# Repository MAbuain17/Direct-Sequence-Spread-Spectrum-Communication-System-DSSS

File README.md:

# DSSS Lab

**Configurable spread-spectrum hardware, receiver experiments and a multiuser CDMA study.**

The project combines a 2 MHz bench implementation with a configurable I/Q board design. Rev A integrates an STM32G474, dual DAC outputs, receive inputs and digital expansion around a programmable signal chain.

## Configurable hardware — Rev A

| Area | Design |
|---|---|
| Data | User bits, text, hexadecimal payloads, PRBS and repeating patterns |
| Spreading | Selectable LFSR taps, seed, code phase and spreading length; uploaded sequences |
| Modulation | BPSK, QPSK, OOK and continuous-phase 2-FSK in the firmware specification |
| Analogue | Buffered TX I/Q, filtered and protected RX I/Q, four labelled SMA ports |
| Control | USB-C, reset/mode/user buttons, status LEDs and test points |
| Development | SWD/SWO programming, SPI/UART expansion, chip/data/PN/frame signals |
| PCB | 110 × 80 mm, four copper layers, routed nets, ground planes and M3 mounting holes |

The [hardware package](hardware/configurable/README.md) includes the schematic, routed PCB, board renders, component list and control interface.

## Explore the project

| Topic | Open |
|---|---|
| PCB architecture, BOM and renders | [Configurable hardware](hardware/configurable/README.md) |
| Signal modes and USB commands | [Control interface](hardware/configurable/control-interface.md) |
| Original bench build and captures | [Laboratory implementation](hardware/README.md) |
| BER, interference and synchronization | [Simulation results](docs/results.md) |
| Multiuser access, near–far and receiver algorithms | [CDMA extension](docs/cdma.md) |
| Interactive code and receiver study | [CDMA signal explorer](visualizer/index.html) |
| Signal-chain conventions and parameters | [Methodology](docs/methodology.md) |
| Python, MATLAB and Octave setup | [Getting started](docs/getting-started.md) |

## Run Python

From the repository root, using Python 3.10 or later:

```bash
python -m pip install -e .
python -m unittest discover -s tests -v
python examples/burst_link.py
python -m dsss_lab.experiments
python examples/pulse_shaping.py
python examples/cdma_study.py
```

For a smaller run, add `--quick` to the experiment command. CSV files, figures and environment metadata are written to `results/`. Running without installing is also possible with `PYTHONPATH=src` on Linux/macOS; see the Windows guide for PowerShell.

## Run MATLAB

No Communications Toolbox is required. From the repository root:

```matlab
addpath('matlab');
test_dsss;
run_experiments('results/matlab', 12000);
advanced_demo('results/matlab');
```

MATLAB shares deterministic test vectors with Python. Random-number streams differ, so Monte Carlo results should agree statistically, not bit-for-bit. **Python, GNU Octave and native MATLAB pass the published GitHub Actions validation workflows.** Native MATLAB runs automatically when its implementation, shared vectors or workflow changes and remains manually dispatchable.

## What the software explores

| Area | Implemented experiments |
|---|---|
| Data | Random bits, constants, alternating patterns, bursts, UTF-8 text, 8-bit PCM, CRC32 frames |
| Spreading | Exact hardware XNOR recurrence, code phase, autocorrelation, configurable spreading length, two-user Gold-family interference |
| Channels | AWGN; in-band and out-of-band tones; swept interference; burst noise; multipath; symbol-independent Rayleigh fading |
| Receiver | Coherent despreading, known-preamble delay/CFO acquisition, burst phase correction, known-channel matched combining |
| Front end | Carrier offset, phase offset/noise, fractional timing error, ADC clipping/quantization, IQ imbalance, RRC pulse shaping |
| Measurements | BER with Wilson intervals, frame CRC failure rate, acquisition success, raw decision EVM, Welch PSD and 99% occupied bandwidth |
| Coding | Soft repetition decoding with equal information-bit energy as a normalization check |

## BER and interference

At equal information-bit energy, DSSS and ordinary coherent BPSK have the same theoretical BER in AWGN. Spreading's interference behaviour depends on the interferer's spectrum and the receiver. The experiments include cases where DSSS helps and cases where the narrower unspread receiver performs better.

The simulation uses 60,000 bits per AWGN point and 30,000 bits per interference point. Source CSVs include error counts and confidence intervals; seeds and model settings are documented in [methodology](docs/methodology.md).

## From DSSS to CDMA

The [CDMA extension](docs/cdma.md) combines four spread-spectrum users in one channel and compares a matched filter, decorrelator and linear MMSE receiver under code-phase and near–far changes. The sweep records 45 conditions with 12,000 desired-user bits each. A separate [browser explorer](visualizer/index.html) exposes the code correlations, chip waveforms and receiver decisions interactively.

To use the explorer, download or clone the repository and open `visualizer/index.html` in a browser.

## Credits

Project by **Mohamed Abuain**. The university bench implementation was supervised by Prof. Tammam Benmusa. Its circuit reference and source article are recorded in the [design references](docs/attribution.md).

[Software licence](LICENSE.md) · [Changelog](CHANGELOG.md) · [Roadmap](docs/roadmap.md)

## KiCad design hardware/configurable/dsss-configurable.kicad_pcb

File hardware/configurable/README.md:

# Configurable DSSS transceiver — Rev A

A USB-controlled I/Q baseband board built around the STM32G474RET6. The architecture replaces fixed logic with programmable data generation, spreading and symbol mapping, while exposing both analogue channels and digital timing signals for measurement.

**Design:** 110 × 80 mm · four copper layers · 70 circuit components · four SMA ports · USB-C · SWD · SPI/UART expansion.

## Configurable signal chain

```mermaid
flowchart LR
    H[USB host: payload and configuration] --> P[Payload / preamble / CRC]
    P --> S[Programmable spreading]
    N[LFSR taps, seed, length and phase] --> S
    S --> M[BPSK / QPSK / OOK / 2-FSK mapping]
    M --> D[Timer-triggered dual DAC + DMA]
    D --> T[RC filters + I/Q buffers]
    T --> O[TX I / TX Q]
    I[RX I / RX Q] --> A[Input resistors, clamps and RC filters]
    A --> B[Receive buffers + dual ADC]
    B --> R[DMA capture / host analysis]
    S --> G[Chip clock / data / PN / frame header]
```

## Planned operating controls

| Control | Options |
|---|---|
| Payload | User bit string, hexadecimal bytes, UTF-8 text, PRBS, alternating bits, all-zero/all-one and repeating patterns |
| PN sequence | Configurable Fibonacci LFSR order, feedback taps, seed, code phase and spreading length; optional uploaded chip sequence |
| Modulation | BPSK, Gray-mapped QPSK, OOK and continuous-phase 2-FSK |
| Timing | Chip rate, samples per chip, burst duration, frame spacing and repeat count |
| Framing | Preamble, length, payload and CRC32; raw chip mode for scope captures |
| Experiments | I/Q loopback, code mismatch, delay sweeps, burst acquisition and known-pattern BER comparisons |
| Instrumentation | Digital chip clock, data, PN and frame signals; DAC/ADC test pads; status LEDs |

Rev A includes the schematic, routed PCB and control specification. Firmware and board bring-up are the next development stage. The Python/MATLAB simulations remain available for numerical experiments.

## Hardware blocks

| Block | Implementation |
|---|---|
| Processing | STM32G474RET6, LQFP64; Cortex-M4 with hardware timers, DMA, dual DAC and multiple ADCs |
| USB | GCT USB4105 USB-C connector, separate 5.1 kΩ CC pull-downs, USBLC6 protection and 22 Ω data-line resistors |
| Power | USB 5 V, 500 mA PTC, AP2112K 3.3 V regulator; ferrite-filtered analogue rail and local decoupling |
| Clock | 8 MHz crystal with load capacitors; USB clock configuration described in the firmware plan |
| Transmit | PA4/PA5 DAC outputs, 1 kΩ / 1 nF RC filters, TLV9064 unity-gain buffers and 100 Ω output isolation |
| Receive | Series input resistance, Schottky clamps, 1 kΩ / 1 nF RC filtering, TLV9064 buffers and PC0/PC1 ADC inputs |
| Development | SWD/SWO, reset button, boot jumper, mode/user buttons, TX/RX LEDs and SPI/UART header |
| Mechanical | Four M3 mounting holes, separated USB/power, processing and analogue regions, labelled SMA ports |

The SMA connections carry **DC-biased baseband I/Q**, with high-impedance loading. They are not antenna outputs or 50 Ω line drivers. The default development target is 25 kchip/s at four samples/chip; the analogue RC corner is approximately 159 kHz. Rate limits depend on firmware timing, conversion settings and filter response.

## Design files

| File | Contents |
|---|---|
| [KiCad project](dsss-configurable.kicad_pro) | Board rules and project settings |
| [Schematic](dsss-configurable.kicad_sch) | Connected component-level design |
| [PCB](dsss-configurable.kicad_pcb) | Four-layer layout, copper tracks, vias and filled ground planes |
| [Local symbol library](dsss-configurable.kicad_sym) | Embedded component symbols for the project |
| [Schematic preview](renders/schematic.svg) | Browser-readable circuit drawing |
| [Top view](renders/board-top.png) | Component placement and silkscreen |
| [Copper view](renders/copper.svg) | Routed layout |
| [Bill of materials](bom.csv) | References, values and footprints |
| [Pin map](pin-map.md) | MCU peripheral and connector assignments |
| [Control interface](control-interface.md) | Proposed USB commands, modes and frame format |
| [Design review](design-review.md) | Connectivity checks and next review items |

Open `dsss-configurable.kicad_pro` in KiCad 10. The standard footprint and 3D model libraries supply the component geometry; the local symbol library is included in the project.

## Component references

- [ST STM32G474RE datasheet](https://www.st.com/resource/en/datasheet/stm32g474re.pdf)
- [TI TLV9064](https://www.ti.com/product/TLV9064)
- [Diodes AP2112 datasheet](https://www.diodes.com/datasheet/download/AP2112.pdf)

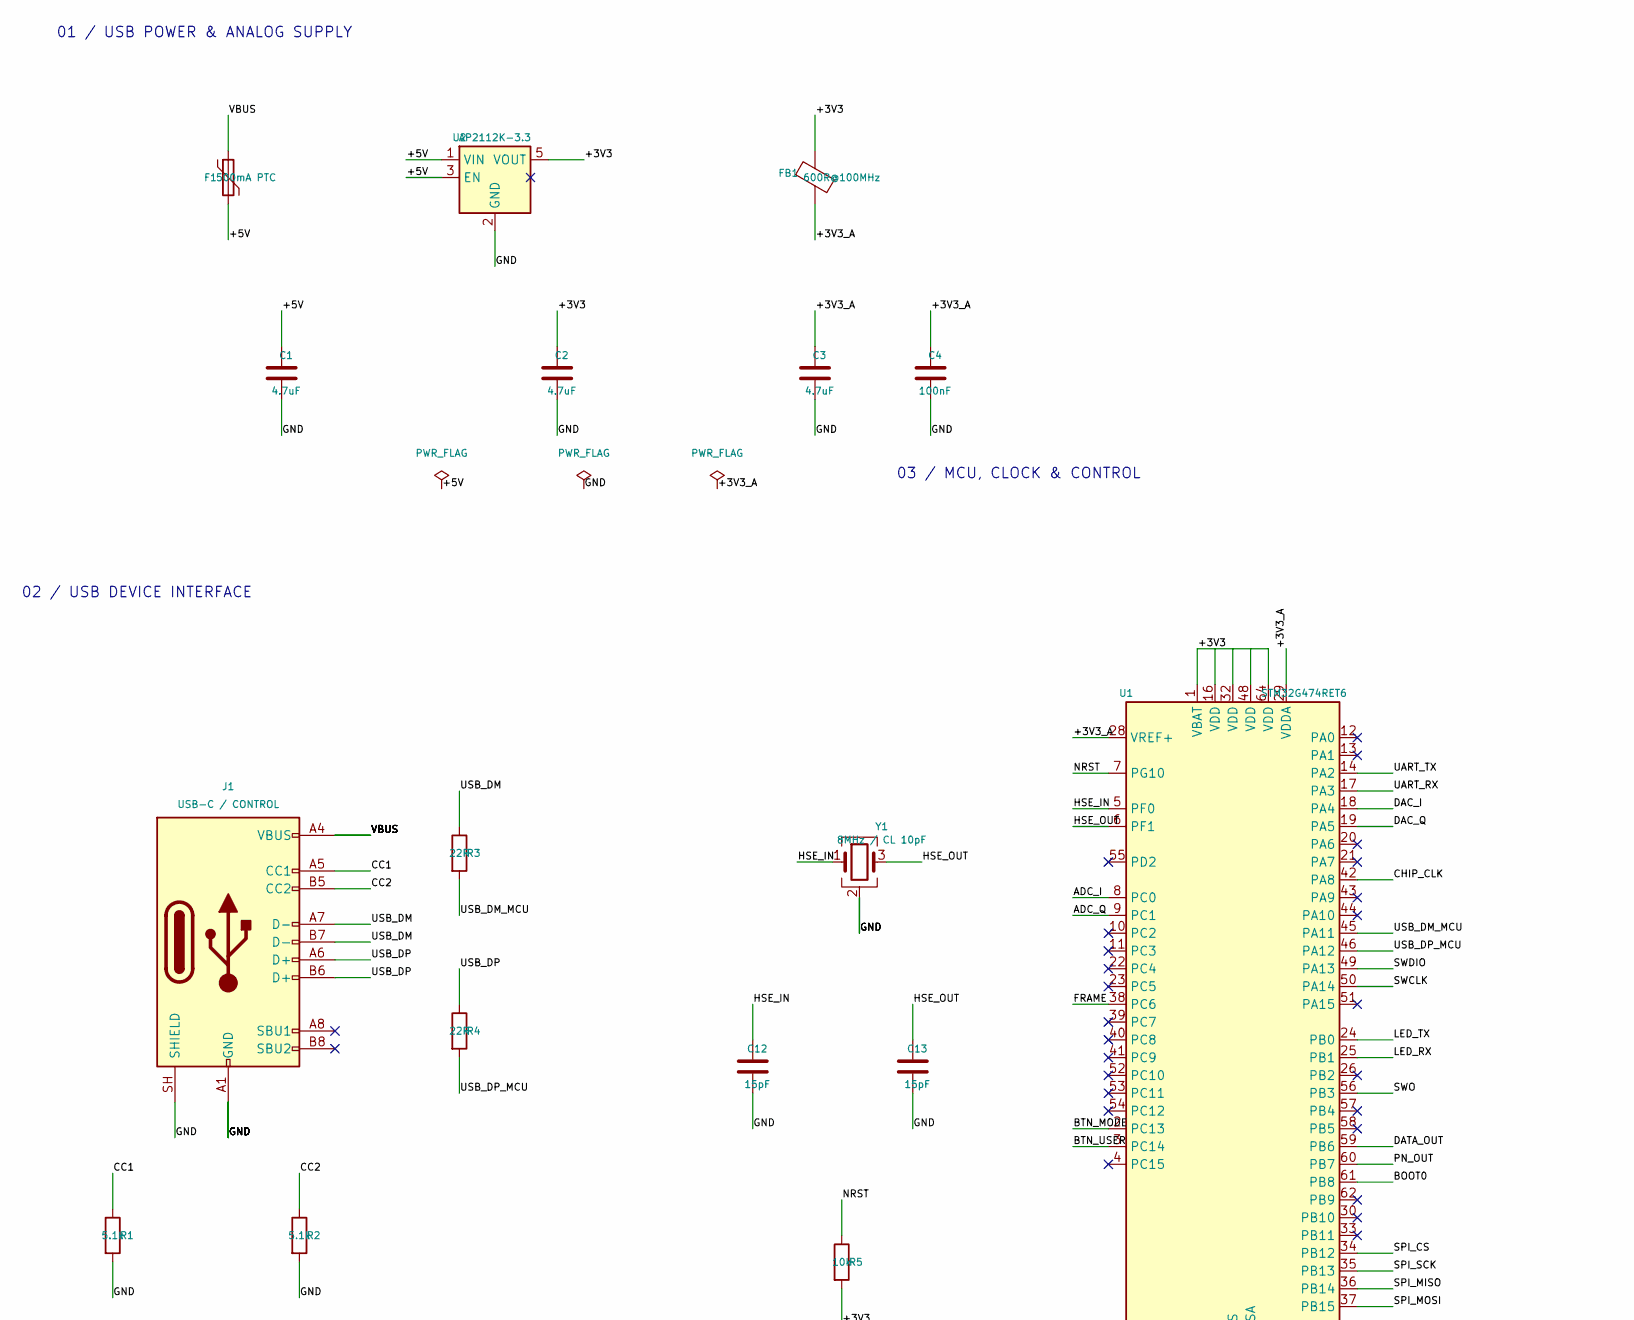
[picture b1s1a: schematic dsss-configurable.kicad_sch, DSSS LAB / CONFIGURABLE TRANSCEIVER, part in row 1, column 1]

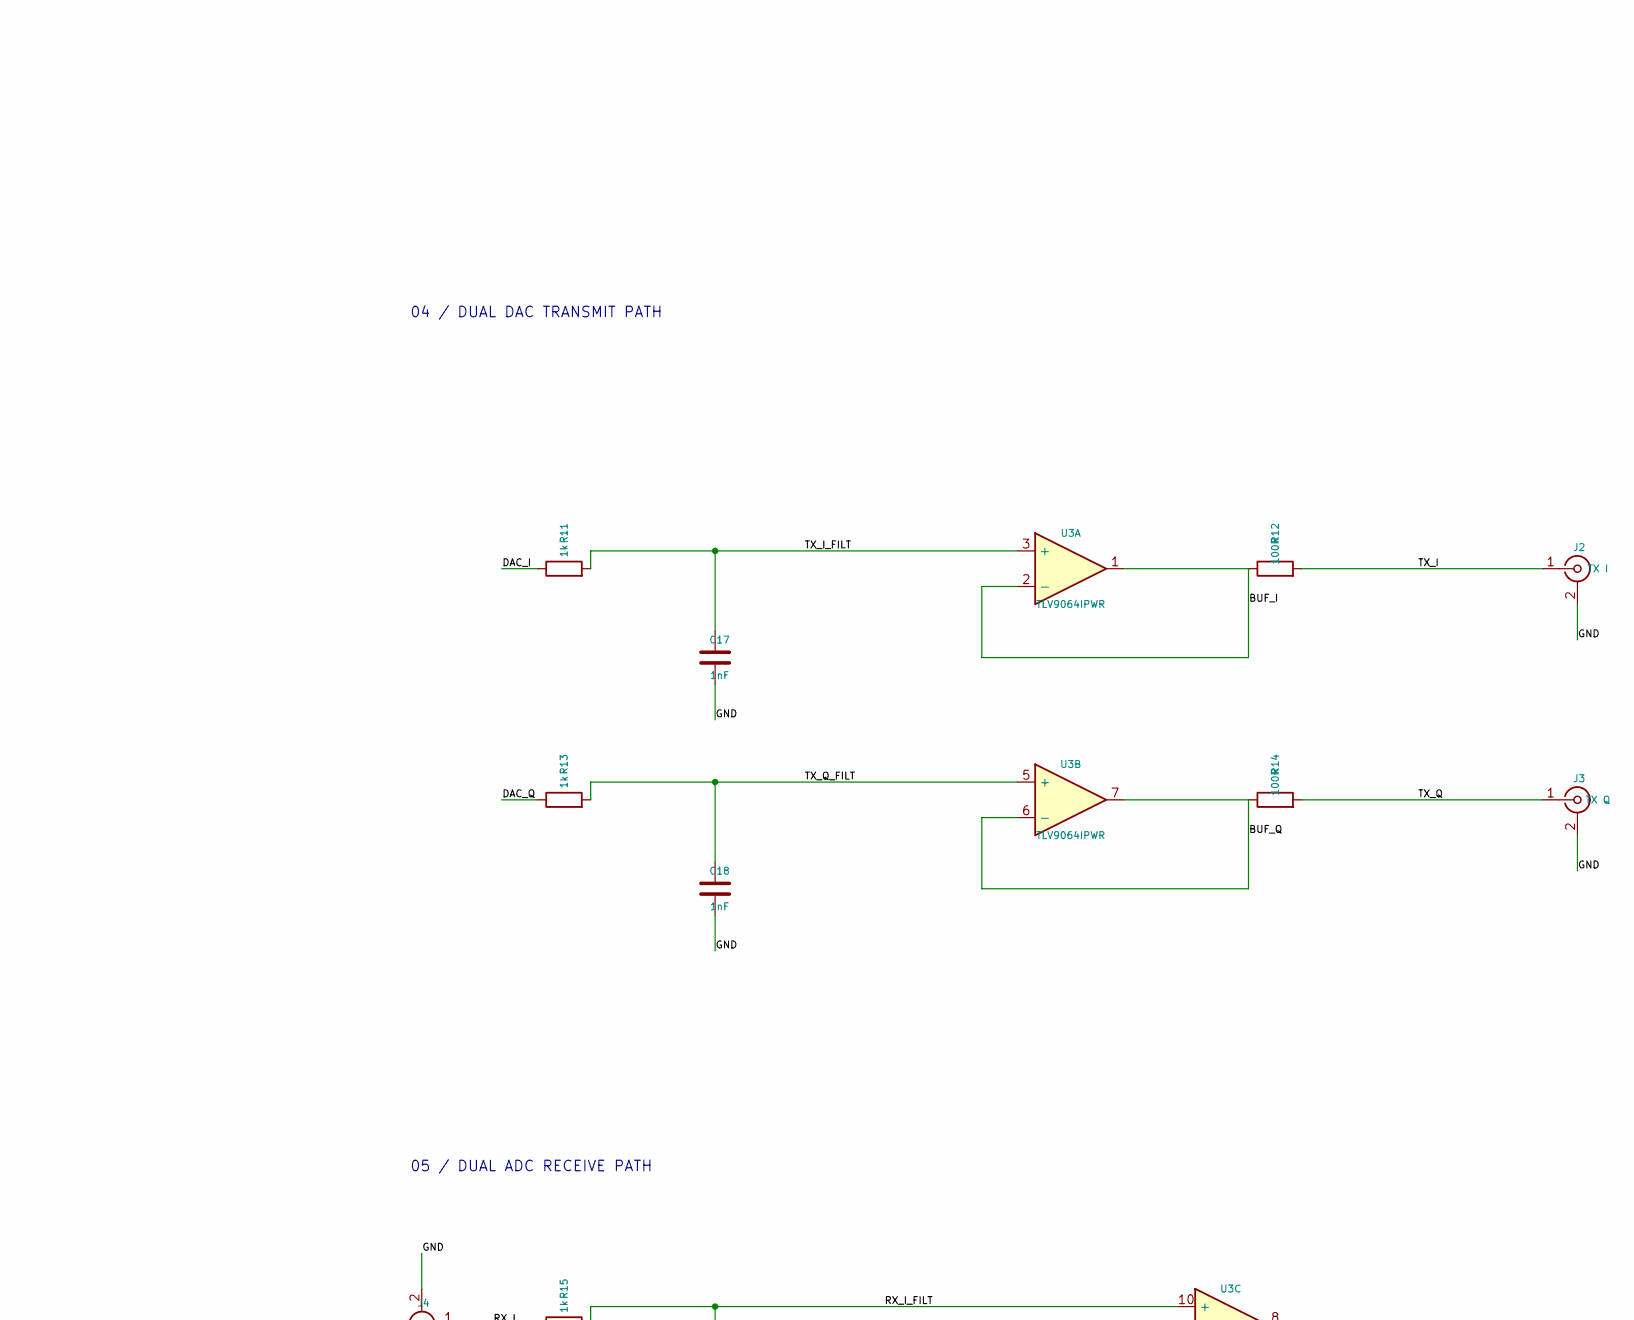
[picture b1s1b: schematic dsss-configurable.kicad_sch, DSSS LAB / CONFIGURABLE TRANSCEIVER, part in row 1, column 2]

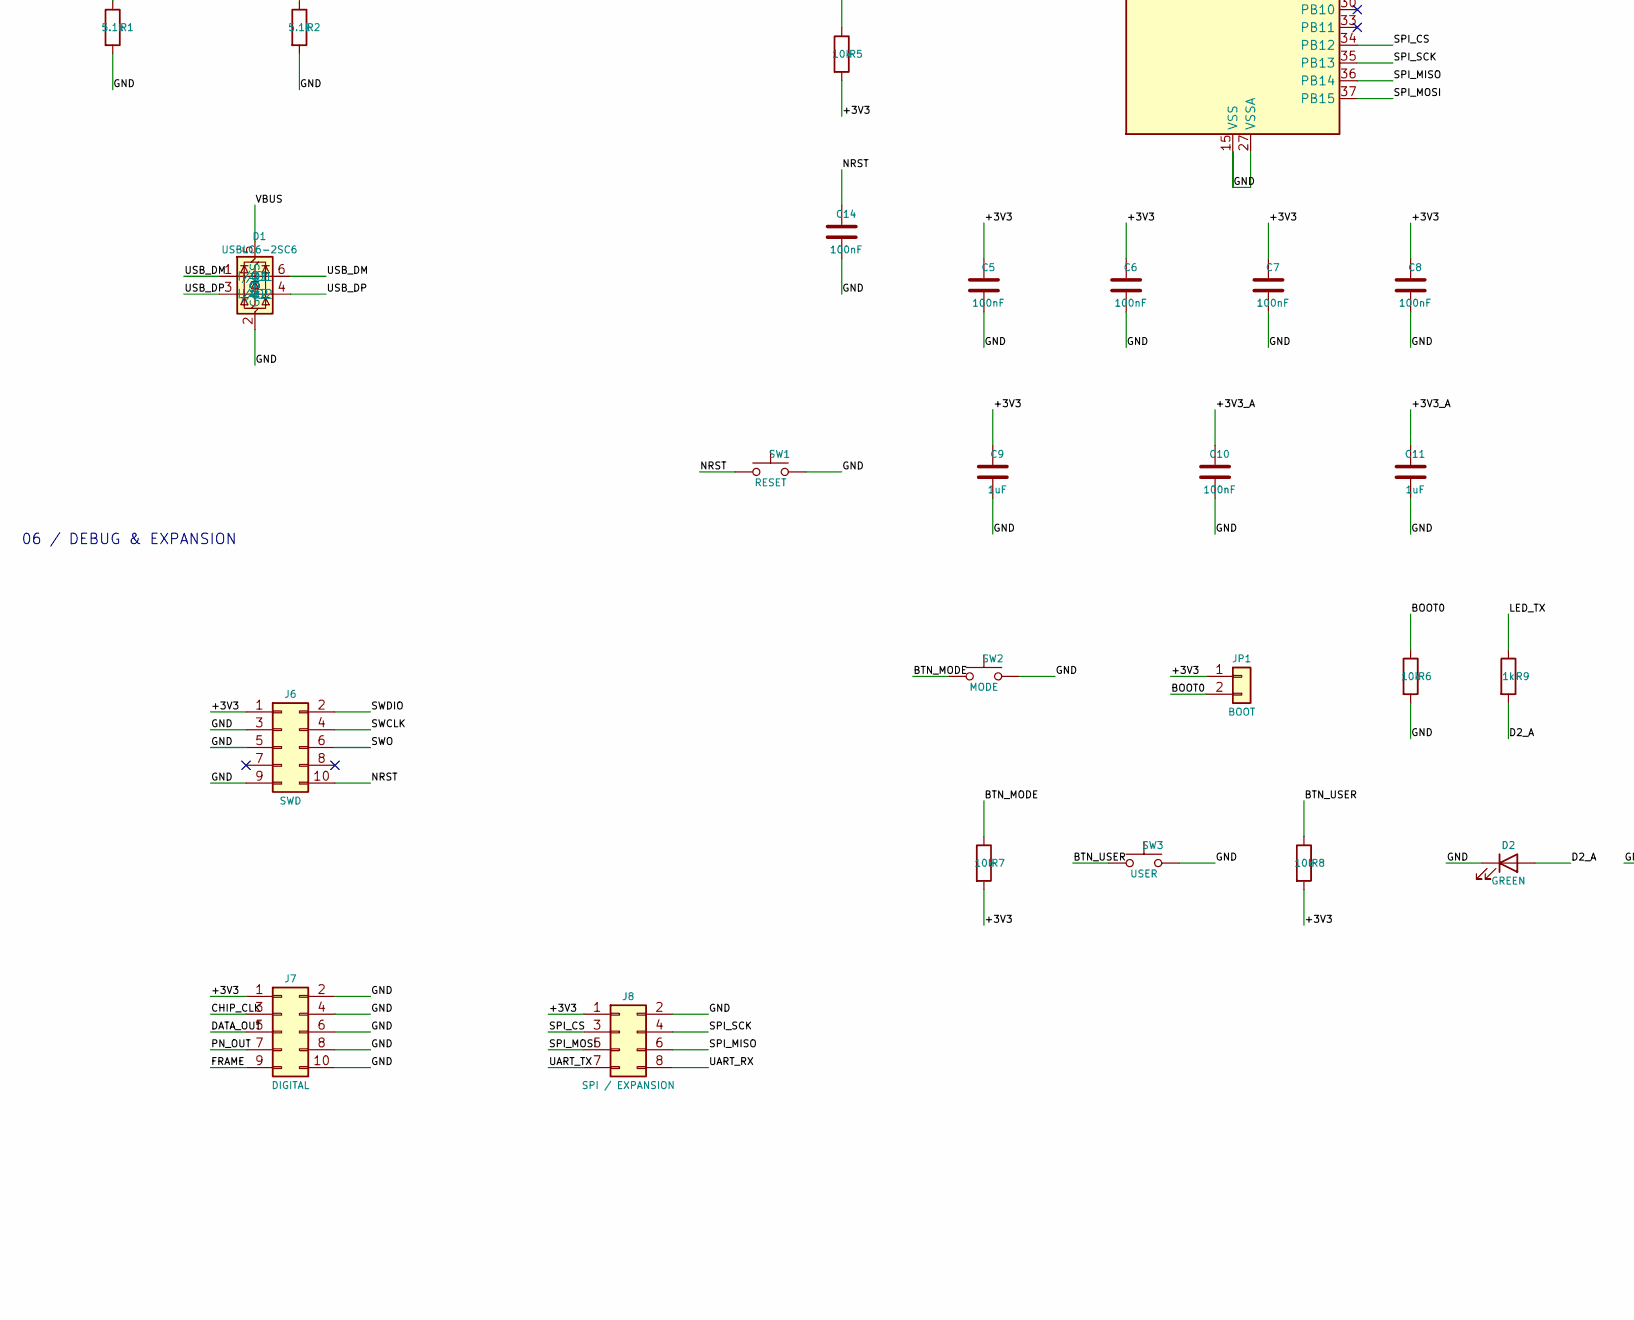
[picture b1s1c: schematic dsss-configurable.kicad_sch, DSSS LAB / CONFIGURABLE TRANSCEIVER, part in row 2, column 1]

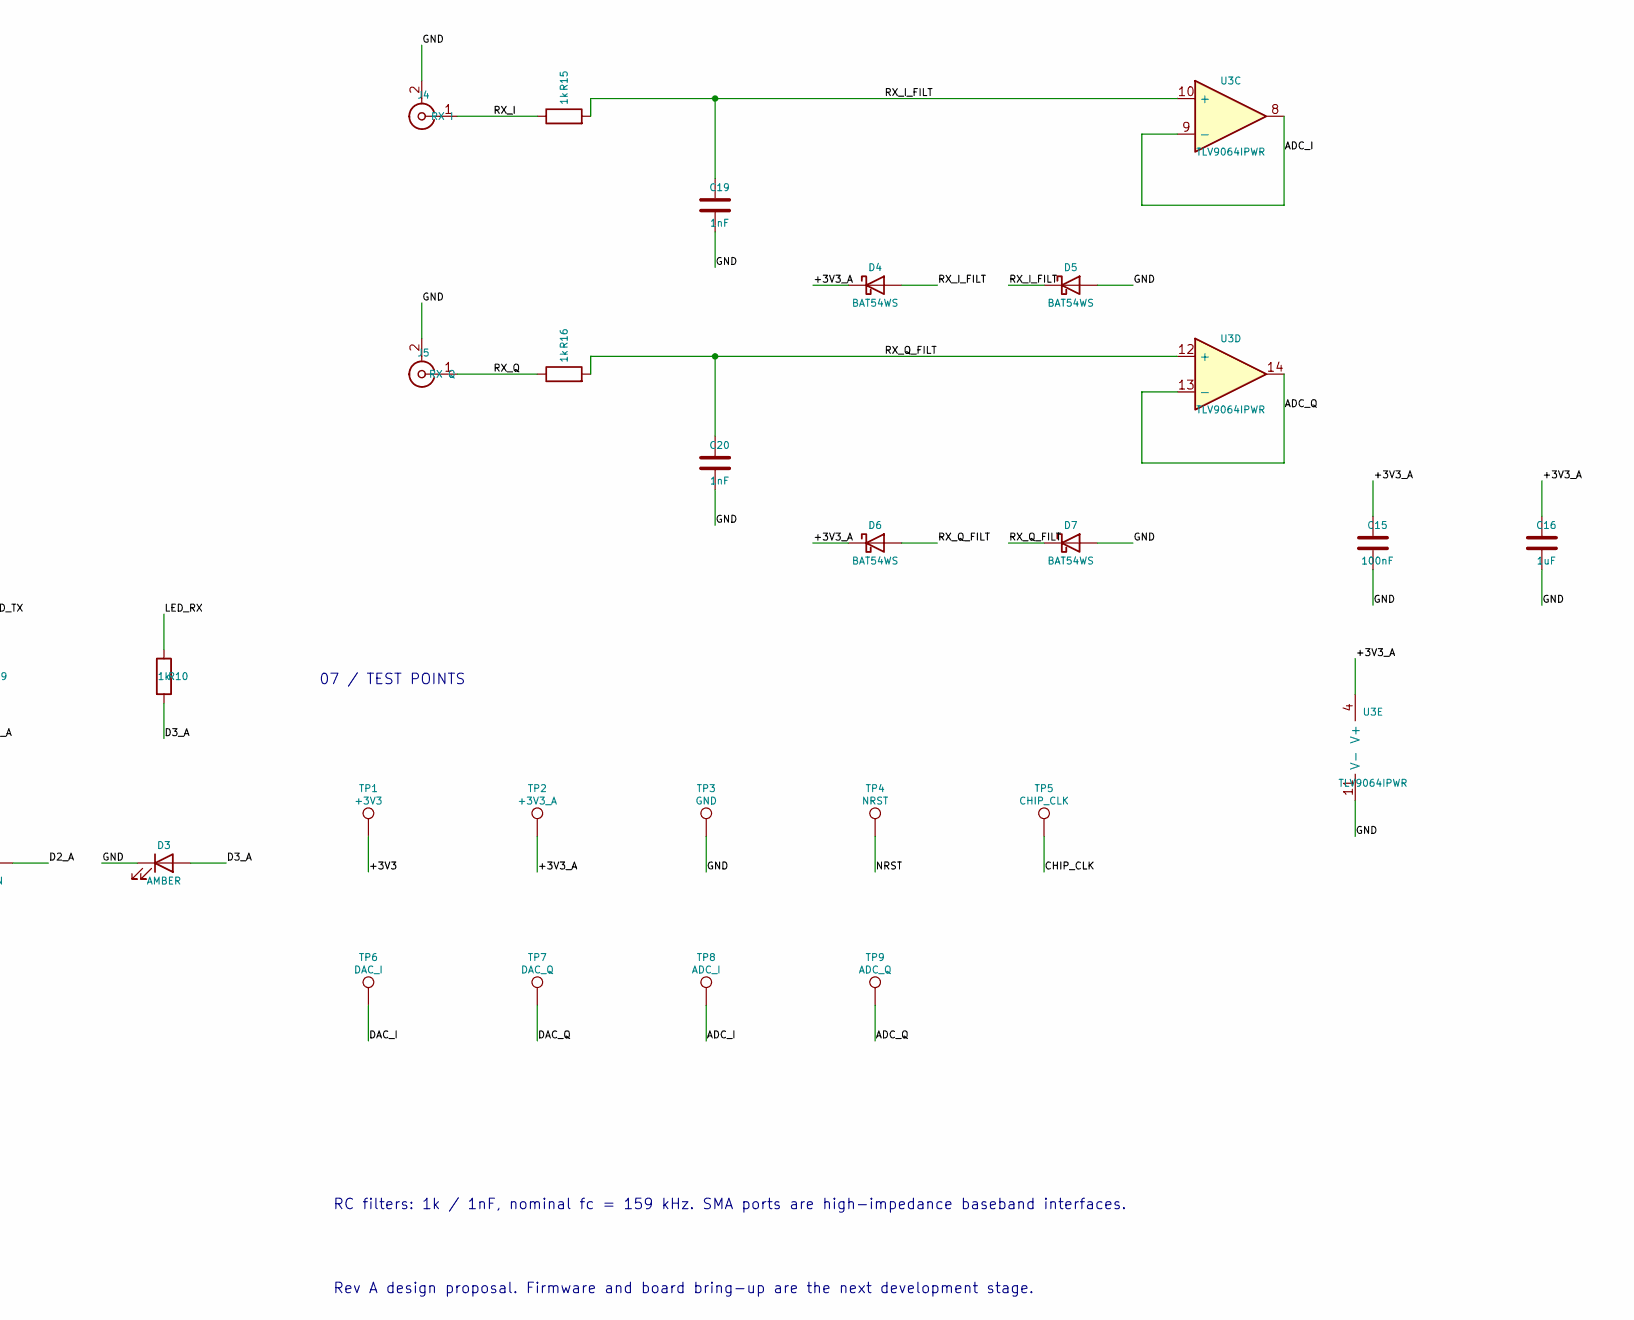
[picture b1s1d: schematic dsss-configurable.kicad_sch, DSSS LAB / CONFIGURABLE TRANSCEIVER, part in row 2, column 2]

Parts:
C1, C2, C3: 4.7uF; C_0603_1608Metric
C4, C5, C6, C7, C8, C10, C14, C15: 100nF; C_0603_1608Metric
C9, C11, C16: 1uF; C_0603_1608Metric
C12, C13: 15pF; C_0603_1608Metric
C17, C18, C19, C20: 1nF; C_0603_1608Metric
D1: USBLC6-2SC6; SOT-23-6
D2: GREEN; LED_0603_1608Metric
D3: AMBER; LED_0603_1608Metric
D4, D5, D6, D7: BAT54WS; D_SOD-323
F1: 500mA PTC; Fuse_1206_3216Metric
FB1: 600R@100MHz; R_0603_1608Metric
J1: USB-C / CONTROL; USB_C_Receptacle_GCT_USB4105-xx-A_16P_TopMnt_Horizontal
J2: TX I; SMA_Amphenol_132291_Vertical
J3: TX Q; SMA_Amphenol_132291_Vertical
J4: RX I; SMA_Amphenol_132291_Vertical
J5: RX Q; SMA_Amphenol_132291_Vertical
J6: SWD; PinHeader_2x05_P1.27mm_Vertical
J7: DIGITAL; PinHeader_2x05_P2.54mm_Vertical
J8: SPI / EXPANSION; PinHeader_2x04_P2.54mm_Vertical
JP1: BOOT; PinHeader_1x02_P2.54mm_Vertical
R1, R2: 5.1k; R_0603_1608Metric
R3, R4: 22R; R_0603_1608Metric
R5, R6, R7, R8: 10k; R_0603_1608Metric
R9, R10, R11, R13, R15, R16: 1k; R_0603_1608Metric
R12, R14: 100R; R_0603_1608Metric
SW1: RESET; SW_SPST_TL3342
SW2: MODE; SW_SPST_TL3342
SW3: USER; SW_SPST_TL3342
TP1: +3V3; TestPoint_Pad_D1.5mm
TP2: +3V3_A; TestPoint_Pad_D1.5mm
TP3: GND; TestPoint_Pad_D1.5mm
TP4: NRST; TestPoint_Pad_D1.5mm
TP5: CHIP_CLK; TestPoint_Pad_D1.5mm
TP6: DAC_I; TestPoint_Pad_D1.5mm
TP7: DAC_Q; TestPoint_Pad_D1.5mm
TP8: ADC_I; TestPoint_Pad_D1.5mm
TP9: ADC_Q; TestPoint_Pad_D1.5mm
U1: STM32G474RET6; LQFP-64_10x10mm_P0.5mm
U2: AP2112K-3.3; SOT-23-5
U3: TLV9064IPWR; TSSOP-14_4.4x5mm_P0.65mm
Y1: 8MHz / CL 10pF; Crystal_SMD_3225-4Pin_3.2x2.5mm

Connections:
+3V3: C2.1, C5.1, C6.1, C7.1, C8.1, C9.1, FB1.1, J6.1, J7.1, J8.1, JP1.1, R5.2, R7.2, R8.2, TP1.1, U1.1 (VBAT), U1.16 (VDD), U1.32 (VDD), U1.48 (VDD), U1.64 (VDD), U2.5 (VOUT)
+3V3_A: C3.1, C4.1, C10.1, C11.1, C15.1, C16.1, D4.1 (K), D6.1 (K), FB1.2, TP2.1, U1.28 (VREF+), U1.29 (VDDA), U3.4 (V+)
+5V: C1.1, F1.2, U2.1 (VIN), U2.3 (EN)
ADC_I: TP8.1, U1.8 (PC0), U3.8, U3.9 (-)
ADC_Q: TP9.1, U1.9 (PC1), U3.13 (-), U3.14
BOOT0: JP1.2, R6.1, U1.61 (PB8)
BTN_MODE: R7.1, SW2.1, U1.2 (PC13)
BTN_USER: R8.1, SW3.1, U1.3 (PC14)
BUF_I: R12.1, U3.1, U3.2 (-)
BUF_Q: R14.1, U3.6 (-), U3.7
CC1: J1.A5 (CC1), R1.1
CC2: J1.B5 (CC2), R2.1
CHIP_CLK: J7.3, TP5.1, U1.42 (PA8)
D2_A: D2.2 (A), R9.2
D3_A: D3.2 (A), R10.2
DAC_I: R11.1, TP6.1, U1.18 (PA4)
DAC_Q: R13.1, TP7.1, U1.19 (PA5)
DATA_OUT: J7.5, U1.59 (PB6)
FRAME: J7.9, U1.38 (PC6)
GND: C1.2, C2.2, C3.2, C4.2, C5.2, C6.2, C7.2, C8.2, C9.2, C10.2, C11.2, C12.2, C13.2, C14.2, C15.2, C16.2, C17.2, C18.2, C19.2, C20.2, D1.2 (GND), D2.1 (K), D3.1 (K), D5.2 (A), D7.2 (A), J1.A1 (GND), J1.A12 (GND), J1.B1 (GND), J1.B12 (GND), J1.SH (SHIELD), J2.2 (Ext), J3.2 (Ext), J4.2 (Ext), J5.2 (Ext), J6.3, J6.5, J6.9, J7.2, J7.4, J7.6, J7.8, J7.10, J8.2, R1.2, R2.2, R6.2, SW1.2, SW2.2, SW3.2, TP3.1, U1.15 (VSS), U1.27 (VSSA), U1.31 (VSS), U1.47 (VSS), U1.63 (VSS), U2.2 (GND), U3.11 (V-), Y1.2 (G), Y1.4 (G)
HSE_IN: C12.1, U1.5 (PF0), Y1.1
HSE_OUT: C13.1, U1.6 (PF1), Y1.3
LED_RX: R10.1, U1.25 (PB1)
LED_TX: R9.1, U1.24 (PB0)
NRST: C14.1, J6.10, R5.1, SW1.1, TP4.1, U1.7 (PG10)
PN_OUT: J7.7, U1.60 (PB7)
RX_I: J4.1 (In), R15.1
RX_I_FILT: C19.1, D4.2 (A), D5.1 (K), R15.2, U3.10 (+)
RX_Q: J5.1 (In), R16.1
RX_Q_FILT: C20.1, D6.2 (A), D7.1 (K), R16.2, U3.12 (+)
SPI_CS: J8.3, U1.34 (PB12)
SPI_MISO: J8.6, U1.36 (PB14)
SPI_MOSI: J8.5, U1.37 (PB15)
SPI_SCK: J8.4, U1.35 (PB13)
SWCLK: J6.4, U1.50 (PA14)
SWDIO: J6.2, U1.49 (PA13)
SWO: J6.6, U1.56 (PB3)
TX_I: J2.1 (In), R12.2
TX_I_FILT: C17.1, R11.2, U3.3 (+)
TX_Q: J3.1 (In), R14.2
TX_Q_FILT: C18.1, R13.2, U3.5 (+)
UART_RX: J8.8, U1.17 (PA3)
UART_TX: J8.7, U1.14 (PA2)
USB_DM: D1.1 (I/O1), D1.6 (I/O1), J1.A7 (D-), J1.B7 (D-), R3.1
USB_DM_MCU: R3.2, U1.45 (PA11)
USB_DP: D1.3 (I/O2), D1.4 (I/O2), J1.A6 (D+), J1.B6 (D+), R4.1
USB_DP_MCU: R4.2, U1.46 (PA12)
VBUS: D1.5 (VBUS), F1.1, J1.A4 (VBUS), J1.A9 (VBUS), J1.B4 (VBUS), J1.B9 (VBUS)

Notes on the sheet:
01 / USB POWER & ANALOG SUPPLY
02 / USB DEVICE INTERFACE
03 / MCU, CLOCK & CONTROL
04 / DUAL DAC TRANSMIT PATH
05 / DUAL ADC RECEIVE PATH
06 / DEBUG & EXPANSION
07 / TEST POINTS
RC filters: 1k / 1nF, nominal fc = 159 kHz. SMA ports are high-impedance baseband interfaces.
Rev A design proposal. Firmware and board bring-up are the next development stage.

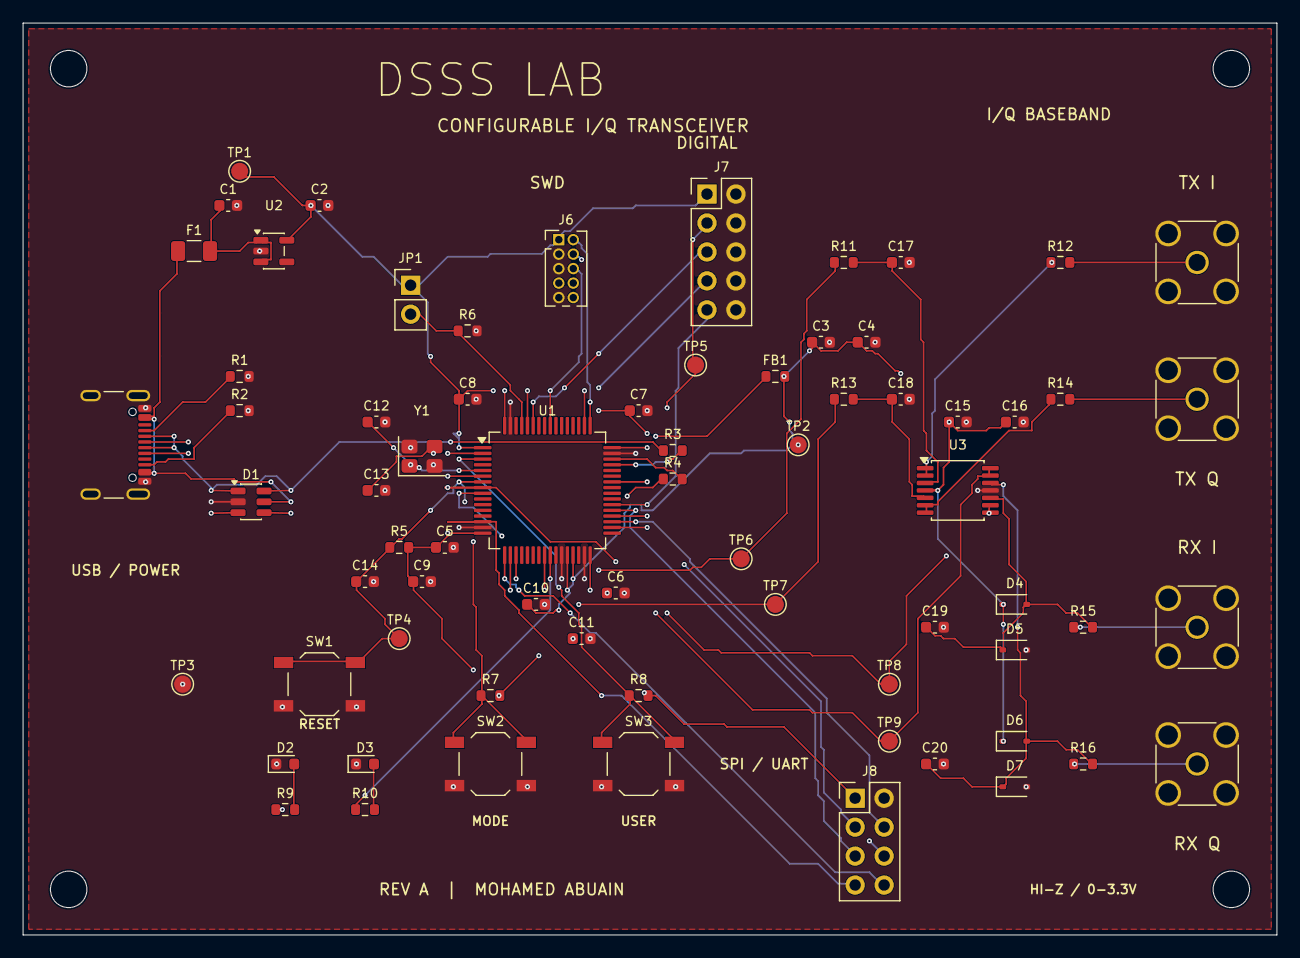
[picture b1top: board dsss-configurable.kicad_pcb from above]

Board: 4 copper layers, 110.0 x 80.0 mm, 74 parts (0 on the bottom side), 48 nets.

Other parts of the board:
H1, H2, H3, H4: MountingHole_3.2mm_M3

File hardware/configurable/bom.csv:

Reference,Value / part,Footprint,Description
J1,USB-C / CONTROL,Connector_USB:USB_C_Receptacle_GCT_USB4105-xx-A_16P_TopMnt_Horizontal,
F1,500mA PTC,Fuse:Fuse_1206_3216Metric,
U2,AP2112K-3.3,Package_TO_SOT_SMD:SOT-23-5,
C1,4.7uF,Capacitor_SMD:C_0603_1608Metric,
C2,4.7uF,Capacitor_SMD:C_0603_1608Metric,
FB1,600R@100MHz,Resistor_SMD:R_0603_1608Metric,
C3,4.7uF,Capacitor_SMD:C_0603_1608Metric,
C4,100nF,Capacitor_SMD:C_0603_1608Metric,
R1,5.1k,Resistor_SMD:R_0603_1608Metric,
R2,5.1k,Resistor_SMD:R_0603_1608Metric,
R3,22R,Resistor_SMD:R_0603_1608Metric,
R4,22R,Resistor_SMD:R_0603_1608Metric,
D1,USBLC6-2SC6,Package_TO_SOT_SMD:SOT-23-6,
U1,STM32G474RET6,Package_QFP:LQFP-64_10x10mm_P0.5mm,
C5,100nF,Capacitor_SMD:C_0603_1608Metric,
C6,100nF,Capacitor_SMD:C_0603_1608Metric,
C7,100nF,Capacitor_SMD:C_0603_1608Metric,
C8,100nF,Capacitor_SMD:C_0603_1608Metric,
C9,1uF,Capacitor_SMD:C_0603_1608Metric,
C10,100nF,Capacitor_SMD:C_0603_1608Metric,
C11,1uF,Capacitor_SMD:C_0603_1608Metric,
Y1,8MHz / CL 10pF,Crystal:Crystal_SMD_3225-4Pin_3.2x2.5mm,
C12,15pF,Capacitor_SMD:C_0603_1608Metric,
C13,15pF,Capacitor_SMD:C_0603_1608Metric,
R5,10k,Resistor_SMD:R_0603_1608Metric,
C14,100nF,Capacitor_SMD:C_0603_1608Metric,
R6,10k,Resistor_SMD:R_0603_1608Metric,
JP1,BOOT,Connector_PinHeader_2.54mm:PinHeader_1x02_P2.54mm_Vertical,
SW1,RESET,Button_Switch_SMD:SW_SPST_TL3342,
SW2,MODE,Button_Switch_SMD:SW_SPST_TL3342,
SW3,USER,Button_Switch_SMD:SW_SPST_TL3342,
R7,10k,Resistor_SMD:R_0603_1608Metric,
R8,10k,Resistor_SMD:R_0603_1608Metric,
R9,1k,Resistor_SMD:R_0603_1608Metric,
D2,GREEN,LED_SMD:LED_0603_1608Metric,
R10,1k,Resistor_SMD:R_0603_1608Metric,
D3,AMBER,LED_SMD:LED_0603_1608Metric,
U3,TLV9064IPWR,Package_SO:TSSOP-14_4.4x5mm_P0.65mm,
C15,100nF,Capacitor_SMD:C_0603_1608Metric,
C16,1uF,Capacitor_SMD:C_0603_1608Metric,
R11,1k,Resistor_SMD:R_0603_1608Metric,
C17,1nF,Capacitor_SMD:C_0603_1608Metric,
R12,100R,Resistor_SMD:R_0603_1608Metric,
R13,1k,Resistor_SMD:R_0603_1608Metric,
C18,1nF,Capacitor_SMD:C_0603_1608Metric,
R14,100R,Resistor_SMD:R_0603_1608Metric,
R15,1k,Resistor_SMD:R_0603_1608Metric,
C19,1nF,Capacitor_SMD:C_0603_1608Metric,
D4,BAT54WS,Diode_SMD:D_SOD-323,
D5,BAT54WS,Diode_SMD:D_SOD-323,
R16,1k,Resistor_SMD:R_0603_1608Metric,
C20,1nF,Capacitor_SMD:C_0603_1608Metric,
D6,BAT54WS,Diode_SMD:D_SOD-323,
D7,BAT54WS,Diode_SMD:D_SOD-323,
J2,TX I,Connector_Coaxial:SMA_Amphenol_132291_Vertical,
J3,TX Q,Connector_Coaxial:SMA_Amphenol_132291_Vertical,
J4,RX I,Connector_Coaxial:SMA_Amphenol_132291_Vertical,
J5,RX Q,Connector_Coaxial:SMA_Amphenol_132291_Vertical,
J6,SWD,Connector_PinHeader_1.27mm:PinHeader_2x05_P1.27mm_Vertical,
J7,DIGITAL,Connector_PinHeader_2.54mm:PinHeader_2x05_P2.54mm_Vertical,
J8,SPI / EXPANSION,Connector_PinHeader_2.54mm:PinHeader_2x04_P2.54mm_Vertical,
TP1,+3V3,TestPoint:TestPoint_Pad_D1.5mm,
TP2,+3V3_A,TestPoint:TestPoint_Pad_D1.5mm,
TP3,GND,TestPoint:TestPoint_Pad_D1.5mm,
TP4,NRST,TestPoint:TestPoint_Pad_D1.5mm,
TP5,CHIP_CLK,TestPoint:TestPoint_Pad_D1.5mm,
TP6,DAC_I,TestPoint:TestPoint_Pad_D1.5mm,
TP7,DAC_Q,TestPoint:TestPoint_Pad_D1.5mm,
TP8,ADC_I,TestPoint:TestPoint_Pad_D1.5mm,
TP9,ADC_Q,TestPoint:TestPoint_Pad_D1.5mm,
